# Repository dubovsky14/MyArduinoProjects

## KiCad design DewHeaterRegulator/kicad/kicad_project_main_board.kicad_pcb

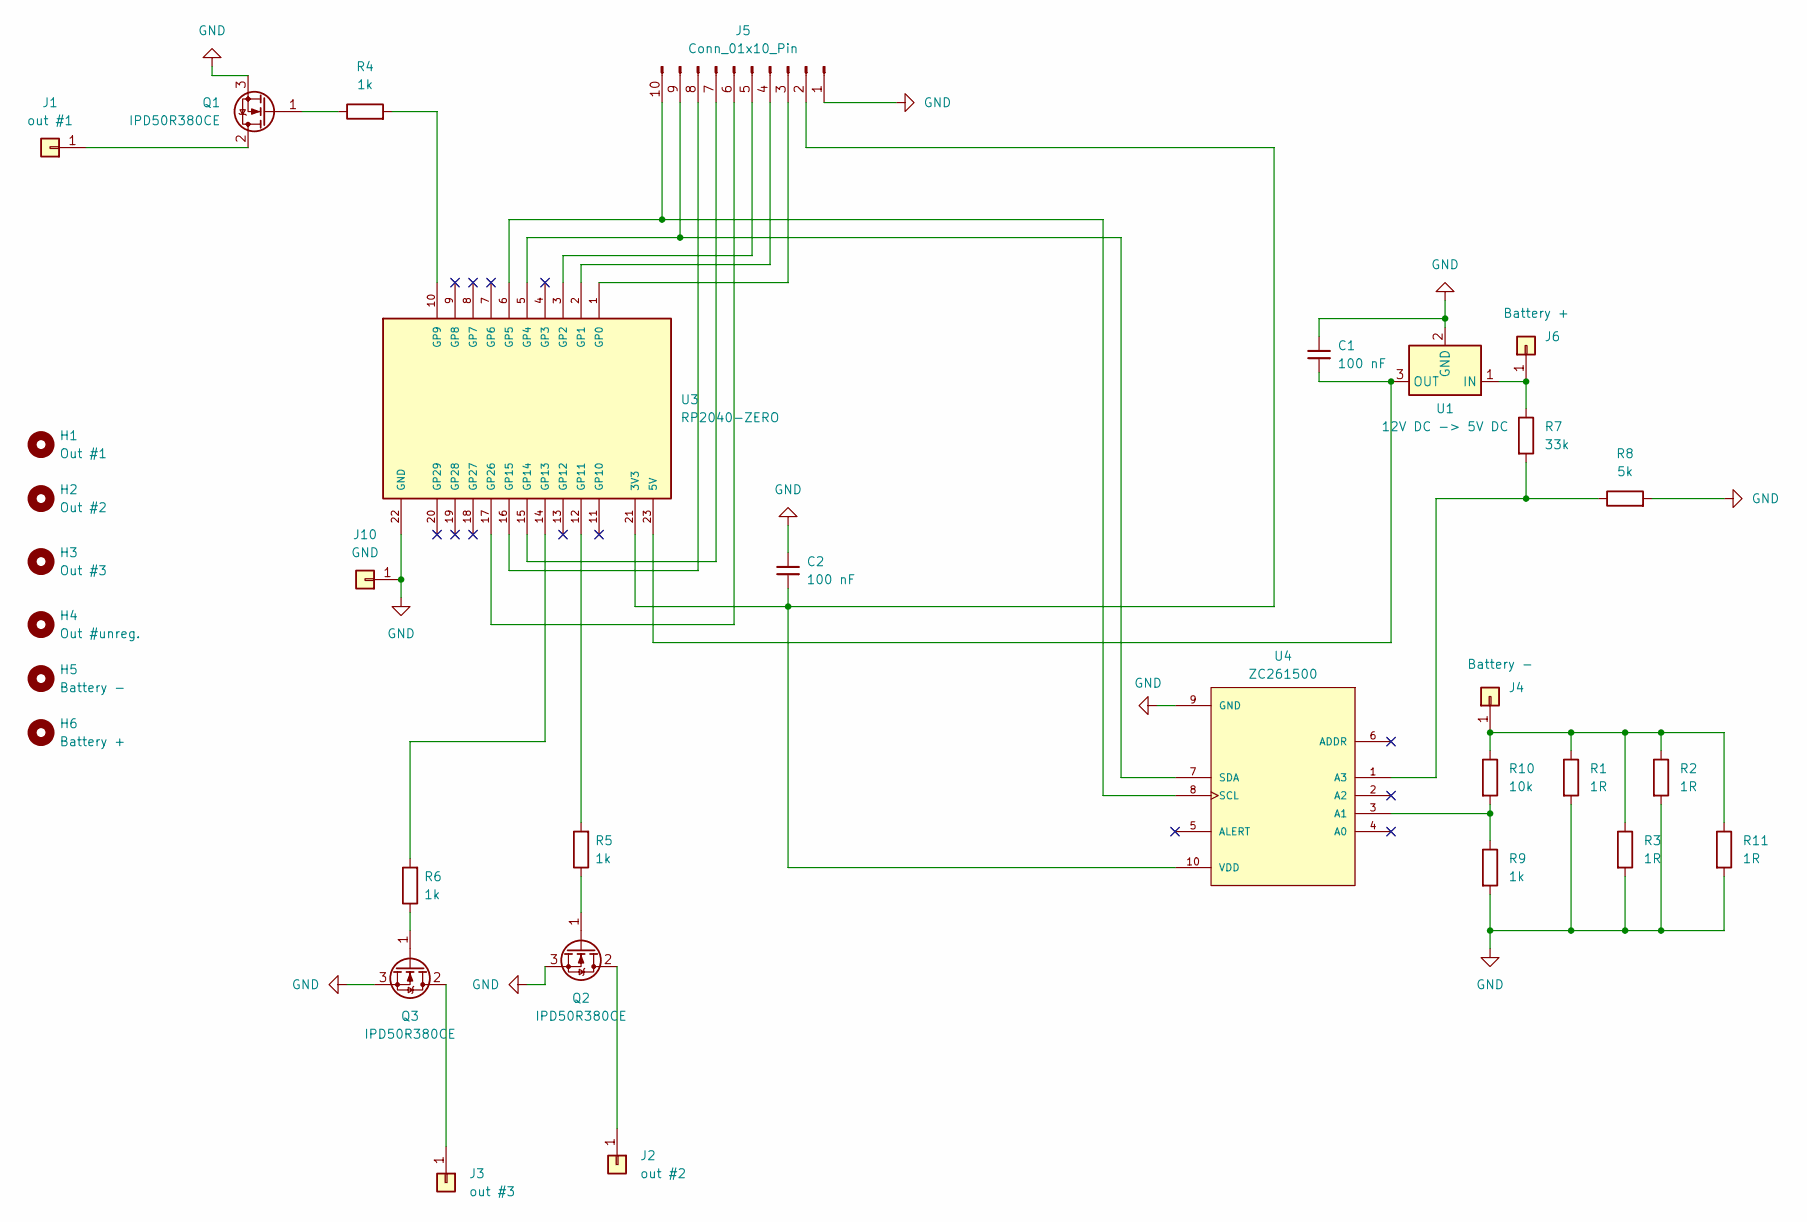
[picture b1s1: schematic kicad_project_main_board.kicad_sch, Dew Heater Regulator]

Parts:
C1, C2: 100 nF; C_Rect_L4.0mm_W2.5mm_P2.50mm
H1: Out #1; MountingHole_3.2mm_M3
H2: Out #2; MountingHole_3.2mm_M3
H3: Out #3; MountingHole_3.2mm_M3
H4: Out #unreg.; MountingHole_3.2mm_M3
H5: Battery -; MountingHole_3.2mm_M3
H6: Battery +; MountingHole_3.2mm_M3
J1: out #1; SolderWire-4sqmm_1x01_D3mm_OD6mm
J2: out #2; SolderWire-4sqmm_1x01_D3mm_OD6mm
J3: out #3; SolderWire-4sqmm_1x01_D3mm_OD6mm
J4: Battery -; SolderWire-4sqmm_1x01_D3mm_OD6mm
J5: Conn_01x10_Pin; PinHeader_1x10_P2.54mm_Vertical
J6: Battery +; SolderWire-4sqmm_1x01_D3mm_OD6mm
J10: GND; SolderWire-4sqmm_1x01_D3mm_OD6mm
Q1, Q2, Q3: IPD50R380CE; TO-252-2
R1, R2, R3, R11: 1R; R_Bare_Metal_Element_L16.3mm_W4.8mm_P15.30mm
R4, R5, R6, R9: 1k; R_Axial_DIN0204_L3.6mm_D1.6mm_P7.62mm_Horizontal
R7: 33k; R_Axial_DIN0204_L3.6mm_D1.6mm_P7.62mm_Horizontal
R8: 5k; R_Axial_DIN0204_L3.6mm_D1.6mm_P7.62mm_Horizontal
R10: 10k; R_Axial_DIN0204_L3.6mm_D1.6mm_P7.62mm_Horizontal
U1: 12V DC -> 5V DC; Converter_DCDC_Murata_OKI-78SR_Vertical
U3: RP2040-ZERO; MODULE_RP2040-ZERO; MPN RP2040-ZERO
U4: ZC261500; MODULE_ZC261500; MPN ZC261500

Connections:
GND: C1.1, C2.1, J5.1, J10.1 (Pin_1_1), Q1.3 (S), Q2.3 (S), Q3.3 (S), R1.2, R2.2, R3.2, R8.2, R9.2, R11.2, U1.2 (GND), U3.22 (GND), U4.9 (GND); also elsewhere on the board
unnamed: J1.1 (Pin_1_1), Q1.2 (D)
unnamed: J2.1 (Pin_1_1), Q2.2 (D)
unnamed: J3.1 (Pin_1_1), Q3.2 (D)
unnamed: J4.1 (Pin_1_1), R1.1, R2.1, R3.1, R10.1, R11.1
unnamed 5: C2.2, J5.2, U3.21 (3V3), U4.10 (VDD); also elsewhere on the board
unnamed: J5.3, U3.1 (GP0)
unnamed: J5.4, U3.2 (GP1)
unnamed: J5.5, U3.3 (GP2)
unnamed: J5.6, U3.17 (GP26)
unnamed: J5.7, U3.15 (GP14)
unnamed: J5.8, U3.16 (GP15)
unnamed 12: J5.9, U3.5 (GP4), U4.7 (SDA); also elsewhere on the board
unnamed 13: J5.10, U3.6 (GP5), U4.8 (SCL); also elsewhere on the board
unnamed: J6.1 (Pin_1_1), R7.1, U1.1 (IN)
unnamed: Q1.1 (G), R4.1
unnamed: Q2.1 (G), R5.1
unnamed: Q3.1 (G), R6.1
unnamed: C1.2, U1.3 (OUT), U3.23 (5V)
unnamed: R4.2, U3.10 (GP9)
unnamed: R5.2, U3.12 (GP11)
unnamed: R6.2, U3.14 (GP13)
unnamed 22: R9.1, R10.2, U4.3 (A1); also elsewhere on the board
unnamed 23: R7.2, R8.1, U4.1 (A3); also elsewhere on the board

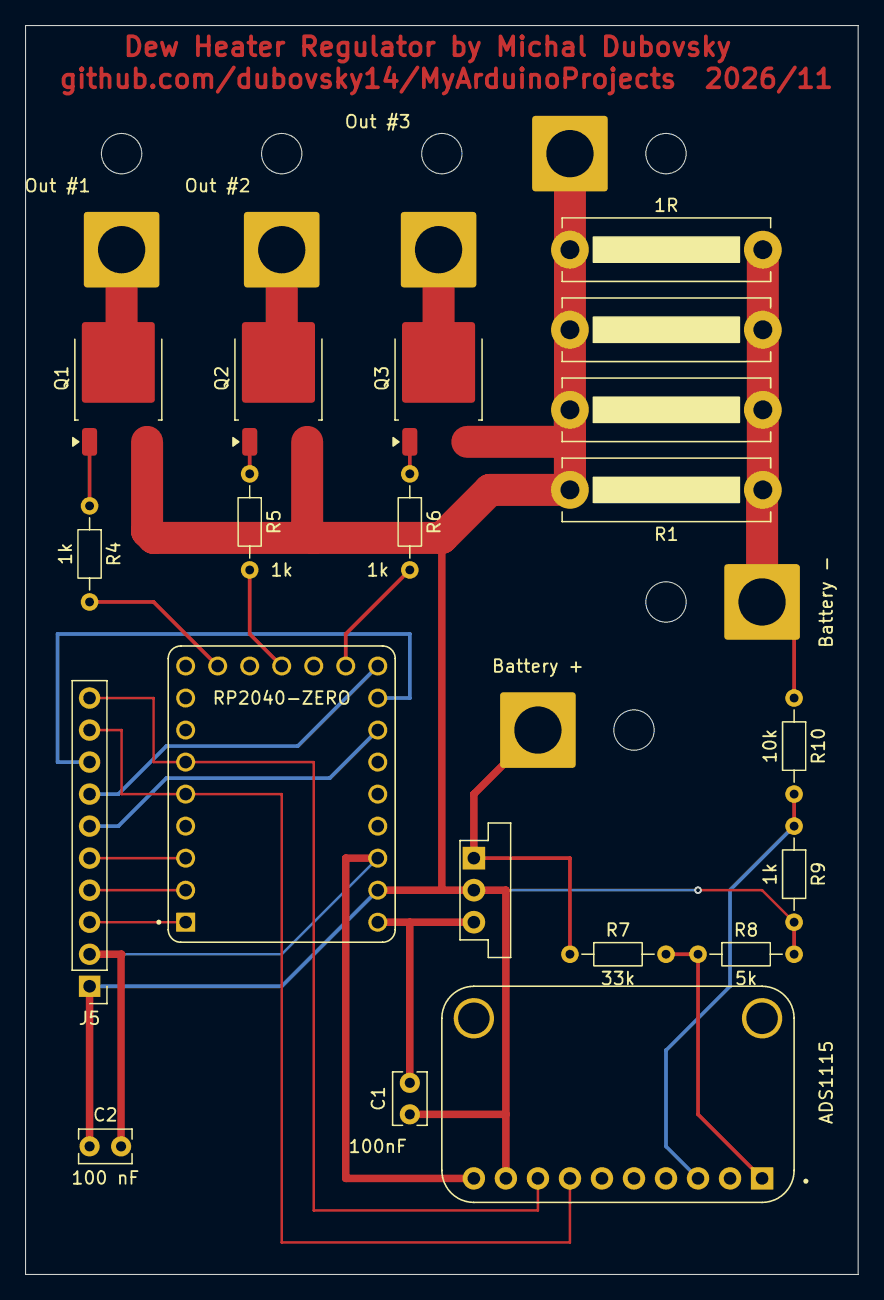
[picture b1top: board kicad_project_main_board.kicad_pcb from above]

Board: 2 copper layers, 66.0 x 99.1 mm, 32 parts (0 on the bottom side), 24 nets.

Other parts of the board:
ADS1115: ZC261500; MODULE_ZC261500

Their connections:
GND: ADS1115.9 (GND); also elsewhere on the board
unnamed 5: ADS1115.10 (VDD); also elsewhere on the board
unnamed 12: ADS1115.7 (SDA); also elsewhere on the board
unnamed 13: ADS1115.8 (SCL); also elsewhere on the board
unnamed 22: ADS1115.3 (A1); also elsewhere on the board
unnamed 23: ADS1115.1 (A3); also elsewhere on the board

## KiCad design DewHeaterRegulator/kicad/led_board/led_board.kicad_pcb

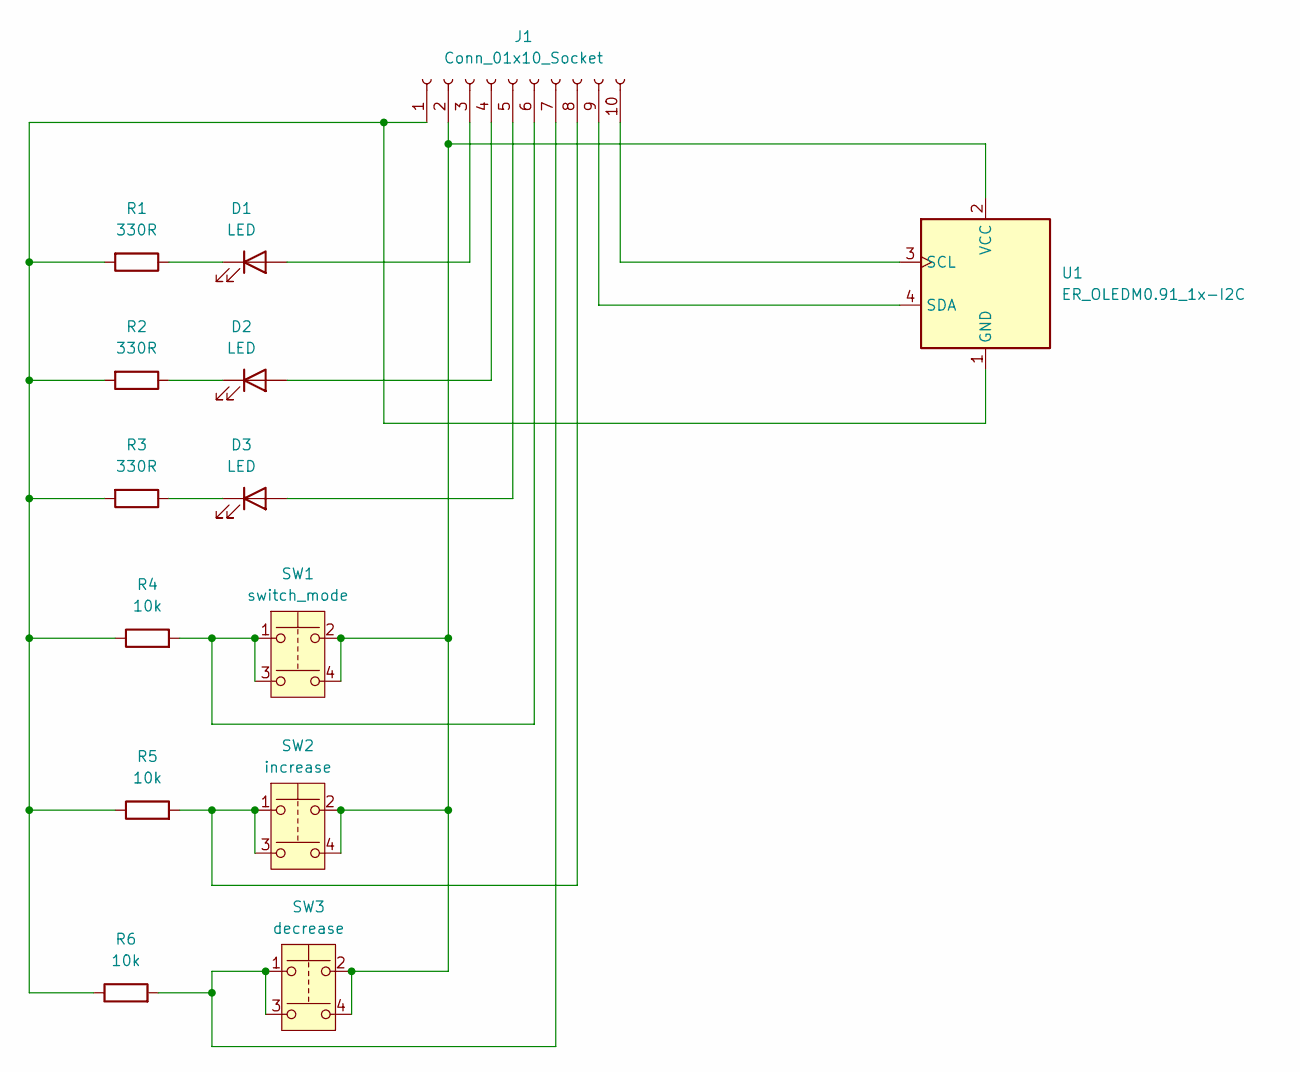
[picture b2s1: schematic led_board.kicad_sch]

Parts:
D1, D2, D3: LED; LED_D5.0mm
J1: Conn_01x10_Socket; PinHeader_1x10_P2.54mm_Vertical
R1, R2, R3: 330R; R_Axial_DIN0309_L9.0mm_D3.2mm_P12.70mm_Horizontal
R4, R5, R6: 10k; R_Axial_DIN0309_L9.0mm_D3.2mm_P12.70mm_Horizontal
SW1: switch_mode; Push_E-Switch_KS01Q01
SW2: increase; Push_E-Switch_KS01Q01
SW3: decrease; Push_E-Switch_KS01Q01
U1: ER_OLEDM0.91_1x-I2C

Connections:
unnamed: D1.2 (A), J1.3
unnamed: D1.1 (K), R1.1
unnamed: D2.2 (A), J1.4
unnamed: D2.1 (K), R2.1
unnamed: D3.2 (A), J1.5
unnamed: D3.1 (K), R3.1
unnamed: J1.1, R1.2, R2.2, R3.2, R4.1, R5.1, R6.1, U1.1 (GND)
unnamed: J1.2, SW1.2, SW1.4, SW2.2, SW2.4, SW3.2, SW3.4, U1.2 (VCC)
unnamed: J1.6, R4.2, SW1.1, SW1.3
unnamed: J1.7, R6.2, SW3.1, SW3.3
unnamed: J1.8, R5.2, SW2.1, SW2.3
unnamed: J1.9, U1.4 (SDA)
unnamed: J1.10, U1.3 (SCL)

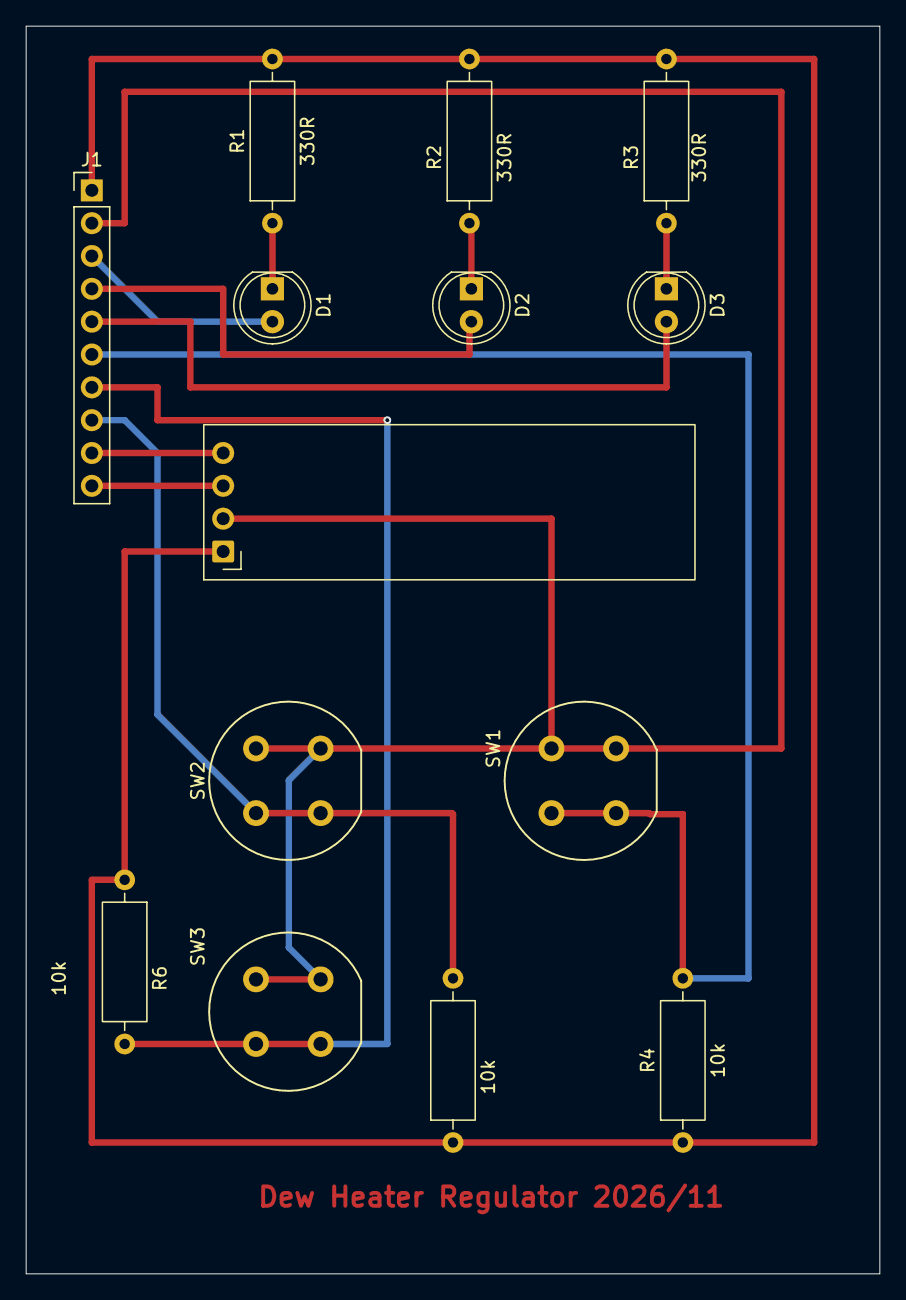
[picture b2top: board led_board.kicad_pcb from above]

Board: 2 copper layers, 66.0 x 96.5 mm, 14 parts (0 on the bottom side), 13 nets.

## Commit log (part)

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2025-01-23 Updating calibration constants in PowerSupplyMonitor
2026-04-28 DewHeaterRegulator: using analogWrite and adding 10,000uF capacitor to the schema
